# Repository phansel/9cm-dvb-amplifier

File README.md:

# 9cm DVB amplifier

This amplifier was designed in early 2019 for use as a telemetry/DVB radio for the CU Boulder COBRA/SRL rocket avionics project.

- ~ 15 watts (41.7 dBm) power output
- ~ 50 dB gain
- 3370 MHz center frequency

Note: editing this project requires at least KiCAD 5.99.

Copyright Paul Hansel (KC1GPW) and Brendan Haines (KE0HSC), 2019

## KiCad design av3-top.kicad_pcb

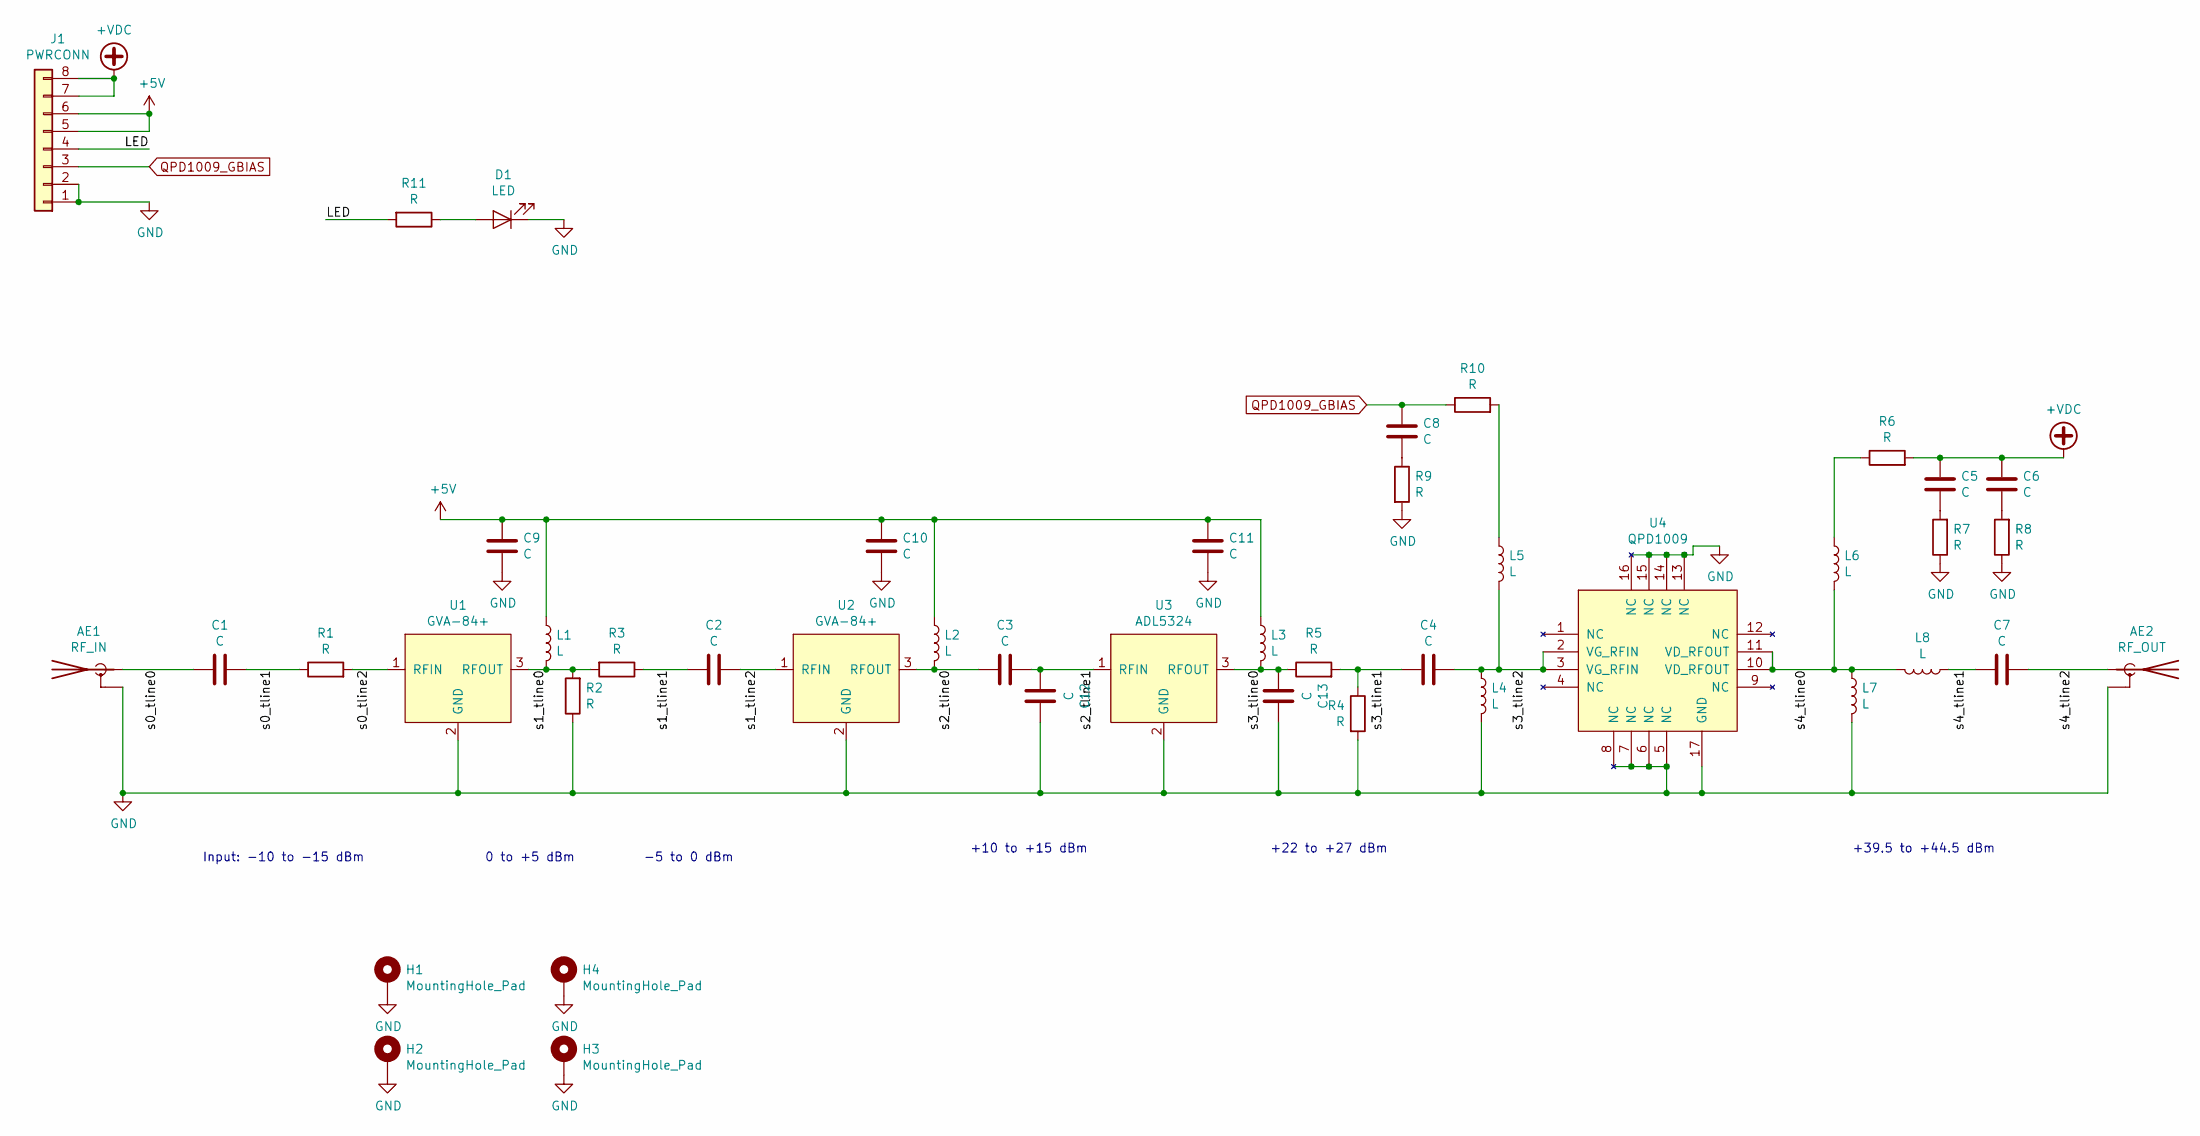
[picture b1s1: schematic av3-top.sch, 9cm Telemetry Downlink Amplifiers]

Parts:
AE1: RF_IN; SMA_Amphenol_132289_EdgeMount
AE2: RF_OUT; SMA_Amphenol_132289_EdgeMount
C1, C2, C3, C9, C10, C12, C13: C; C_0603_1608Metric
C4, C5, C6, C7, C8, C11: C; C_1206_3216Metric
D1: LED; LED_0603_1608Metric
H1, H2, H3, H4: MountingHole_Pad; MountingHole_3.7mm_Pad_Via
J1: PWRCONN; PinHeader_2x04_P2.54mm_Vertical
L1, L2, L3, L4, L5, L7, L8: L; L_0805_2012Metric_Pad1.15x1.40mm_HandSolder
L6: L; L_1206_3216Metric
R1, R2, R3, R4, R5: R; R_0805_2012Metric
R6: R; R_1206_3216Metric
R7, R8, R9, R10: R; R_0805_2012Metric_Pad1.15x1.40mm_HandSolder
R11: R; R_0603_1608Metric_Pad1.05x0.95mm_HandSolder
U1, U2: GVA-84+; SOT-89-3
U3: ADL5324; SOT-89-3
U4: QPD1009; QFN-16-1EP_3x3mm_P0.5mm_EP1.7x1.7mm

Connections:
+5V: C9.2, C10.2, C11.2, J1.5, J1.6, L1.1, L2.1, L3.1
+VDC: C5.2, C6.2, J1.7, J1.8, R6.2
/LED: J1.4, R11.2
/s0_tline0: AE1.1 (A), C1.2
/s0_tline1: C1.1, R1.1
/s0_tline2: R1.2, U1.1 (RFIN)
/s1_tline0: L1.2, R2.2, R3.2, U1.3 (RFOUT)
/s1_tline1: C2.2, R3.1
/s1_tline2: C2.1, U2.1 (RFIN)
/s2_tline0: C3.2, L2.2, U2.3 (RFOUT)
/s2_tline1: C3.1, C12.2, U3.1 (RFIN)
/s3_tline0: C13.2, L3.2, R5.1, U3.3 (RFOUT)
/s3_tline1: C4.2, R4.1, R5.2
/s3_tline2: C4.1, L4.1, L5.2, U4.2 (VG_RFIN), U4.3 (VG_RFIN)
/s4_tline0: L6.2, L7.1, L8.2, U4.10 (VD_RFOUT), U4.11 (VD_RFOUT)
/s4_tline1: C7.2, L8.1
/s4_tline2: AE2.1 (A), C7.1
GND: AE1.2 (Shield), AE2.2 (Shield), C9.1, C10.1, C11.1, C12.1, C13.1, D1.1 (K), H1.1, H2.1, H3.1, H4.1, J1.1, J1.2, L4.2, L7.2, R2.1, R4.2, R7.1, R8.1, R9.2, U1.2 (GND), U2.2 (GND), U3.2 (GND), U4.5 (NC), U4.6 (NC), U4.7 (NC), U4.8 (NC), U4.13 (NC), U4.14 (NC), U4.15 (NC), U4.16 (NC), U4.17 (GND)
unnamed: C5.1, R7.2
unnamed: C6.1, R8.2
unnamed: C8.1, R9.1
unnamed: D1.2 (A), R11.1
unnamed: L5.1, R10.2
unnamed: L6.1, R6.1
QPD1009_GBIAS: C8.2, J1.3, R10.1

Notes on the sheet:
Input: -10 to -15 dBm
0 to +5 dBm
+10 to +15 dBm
+22 to +27 dBm
-5 to 0 dBm
+39.5 to +44.5 dBm

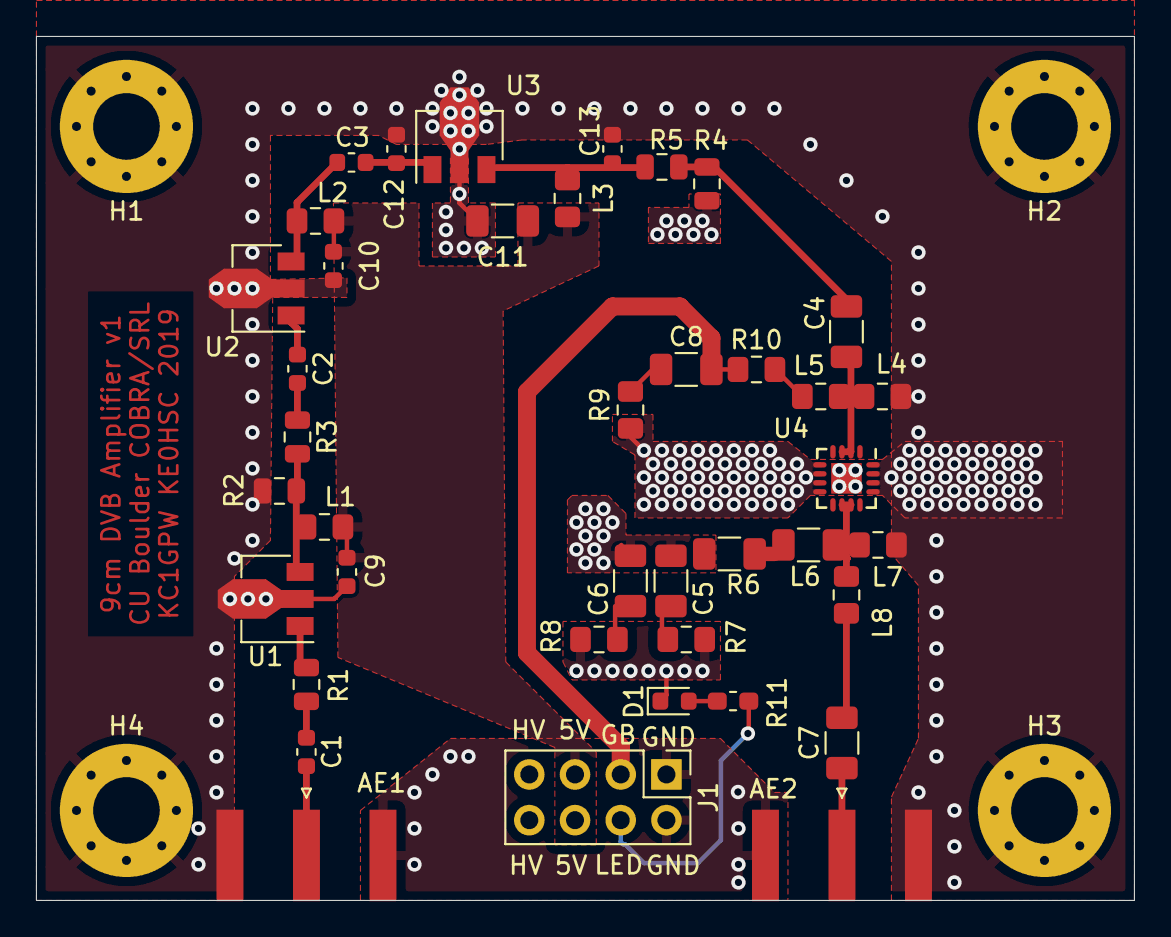
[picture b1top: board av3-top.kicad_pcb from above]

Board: 4 copper layers, 61.0 x 48.0 mm, 44 parts (0 on the bottom side), 25 nets.

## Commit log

2019-11-20 hardware files added
2019-12-27 attribution

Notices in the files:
av3-top.kicad_pcb:
Licensed under CERN OHL v1.2.
